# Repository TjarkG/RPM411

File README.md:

# RPM411
Reverse Engineering of the Vaisala RPM411 Pressur Sensor for the RS41 Radiosonde 

For information about the RS41 see [Bajzos website](https://sondehunt.de/language/en/vaisala-rs41), for schematics of it [the Radiosonde Hardware Repo](https://github.com/bazjo/radiosonde_hardware/tree/master/Vaisala_RS41).

The Schematic is in Kicad format, the Parts overlay in svg and can be edited with Inkscape. Some scans in jpeg are provided too.

Pull requests with improvements, translations and bug fixes are welcome!

# Introduction
The sonde is to be divided into three functional blocks, which are seperated by dotted lines in the Schematic.

* [Power Supply](#powersupply)
* [Microcontroller](#microcontroller)
* [Frontend](#frontend)
* [Connector](#connector)

Microcontroller (hidden by a shield with sticker) and Connector are on the Sonde facing side of the PCB, while the Front end usses almost the entire other side, with its power supply weged in the bottom left corner.

Reverse engineering is simpliefied by the fact that the blocks are essentialy smaller Versions of there RS41 counterparts, sharing many parts. A significant Part of this describtion is therfore the same as for the RS41 with different Part numbers.

# Schematic

## Powersupply
The powersupply (middle right) consists of a Low Dropout Regulator
[TVS70030](http://www.ti.com/lit/ds/symlink/tlv700-q1.pdf) from TI (`U7`), generating 3.3V for the frontend (the MCU is supplyed directly by the Sonde). Pin 4 of the LDO, which is NC according to the datasheet, is decoupled against ground, probably so that pin compatible versions like the [MAX8887](https://datasheets.maximintegrated.com/en/ds/MAX8887-MAX8888.pdf) can be used.

## Microcontroller
The microcontroller is a [STM32F100C8](https://www.st.com/resource/en/datasheet/stm32f100c8.pdf) `U1` from ST in LQFP48 package, the same model as in the Sonde itself, running from an internall clock. Like in the RS41, RC low pass filters are present at many outputs and resistors at many inputs

## Frontend

Electrically, the Frontend is very similar to the RS41's Humindity Messurment, but simplified because there is no temperature Messurment or Heating and all Components are on the PCB. In addition to the Pressure Sensor `P1`, a 15pF reference Capacitor `C33` is available.

The frontend consists of a ring oscillator, whose frequency is varied by variable impedances (e.g. the sensors) inserted into the feedback path with the help of analog switches.

Each ring oscillator is formed by a [74LVC3G04](https://assets.nexperia.com/documents/data-sheet/74LVC3G04.pdf) Triple Inverter `U5`. The three inverters are connected in series. The first and third inverter are feedbacked directly via an RC series element `C26`/`R31`, `R29`/`C23`, the entire ring oscillator via a capacitor `C19`. The ring oscillators can be pulled to +3V by a P-channel MOSFET `Q1` at the first inverter with separate control, which corresponds to ground at the output, to deactivate them.

The feedback path consists of a [74LVC1G32](https://assets.nexperia.com/documents/data-sheet/74LVC1G32.pdf) Or-Gate `U6` used as an Buffer and two resistors `R28` and `R30`, which probably are used for the fine tuning of the resonance frequency. This is followed by three single pole single throw (SPST) switches [TS5A9411](http://www.ti.com/lit/ds/symlink/ts5a9411.pdf) `U2-4`, the NO of which is connected to the output of the buffer and which switch the measuring and reference capacitor either into the feedback network or to ground. `U3` has no connection between COM and the input of the first buffer, where there should normally be a reference capacitor, so this switch does not serve any obvious purpose. However, since it is driven in software like the other two, it can be assumed that the switches have an example-independent non-linear effect on the feedback frequency measured at this switch to compensate for it. Parallel to the switches, fixed feedback is applied via the resistor `R32`.

The measurement output is sent to the MCU via `R8` and `R33`.

## Connector

`J1` connects the Board to the RS41's SPI bus, a clock and a Chip Select, one of which is shared with the EEPROM, as well as 3V MCU voltage shared with the STM32 on the Sonde and the EEPROM and 3.8V from the boost converter used to supply the Frontend via `U7`. From the six Pins that aren't connected on the RS41, five are used for an SWD interface, the MCU Reset pin and an UART and one remains unused.

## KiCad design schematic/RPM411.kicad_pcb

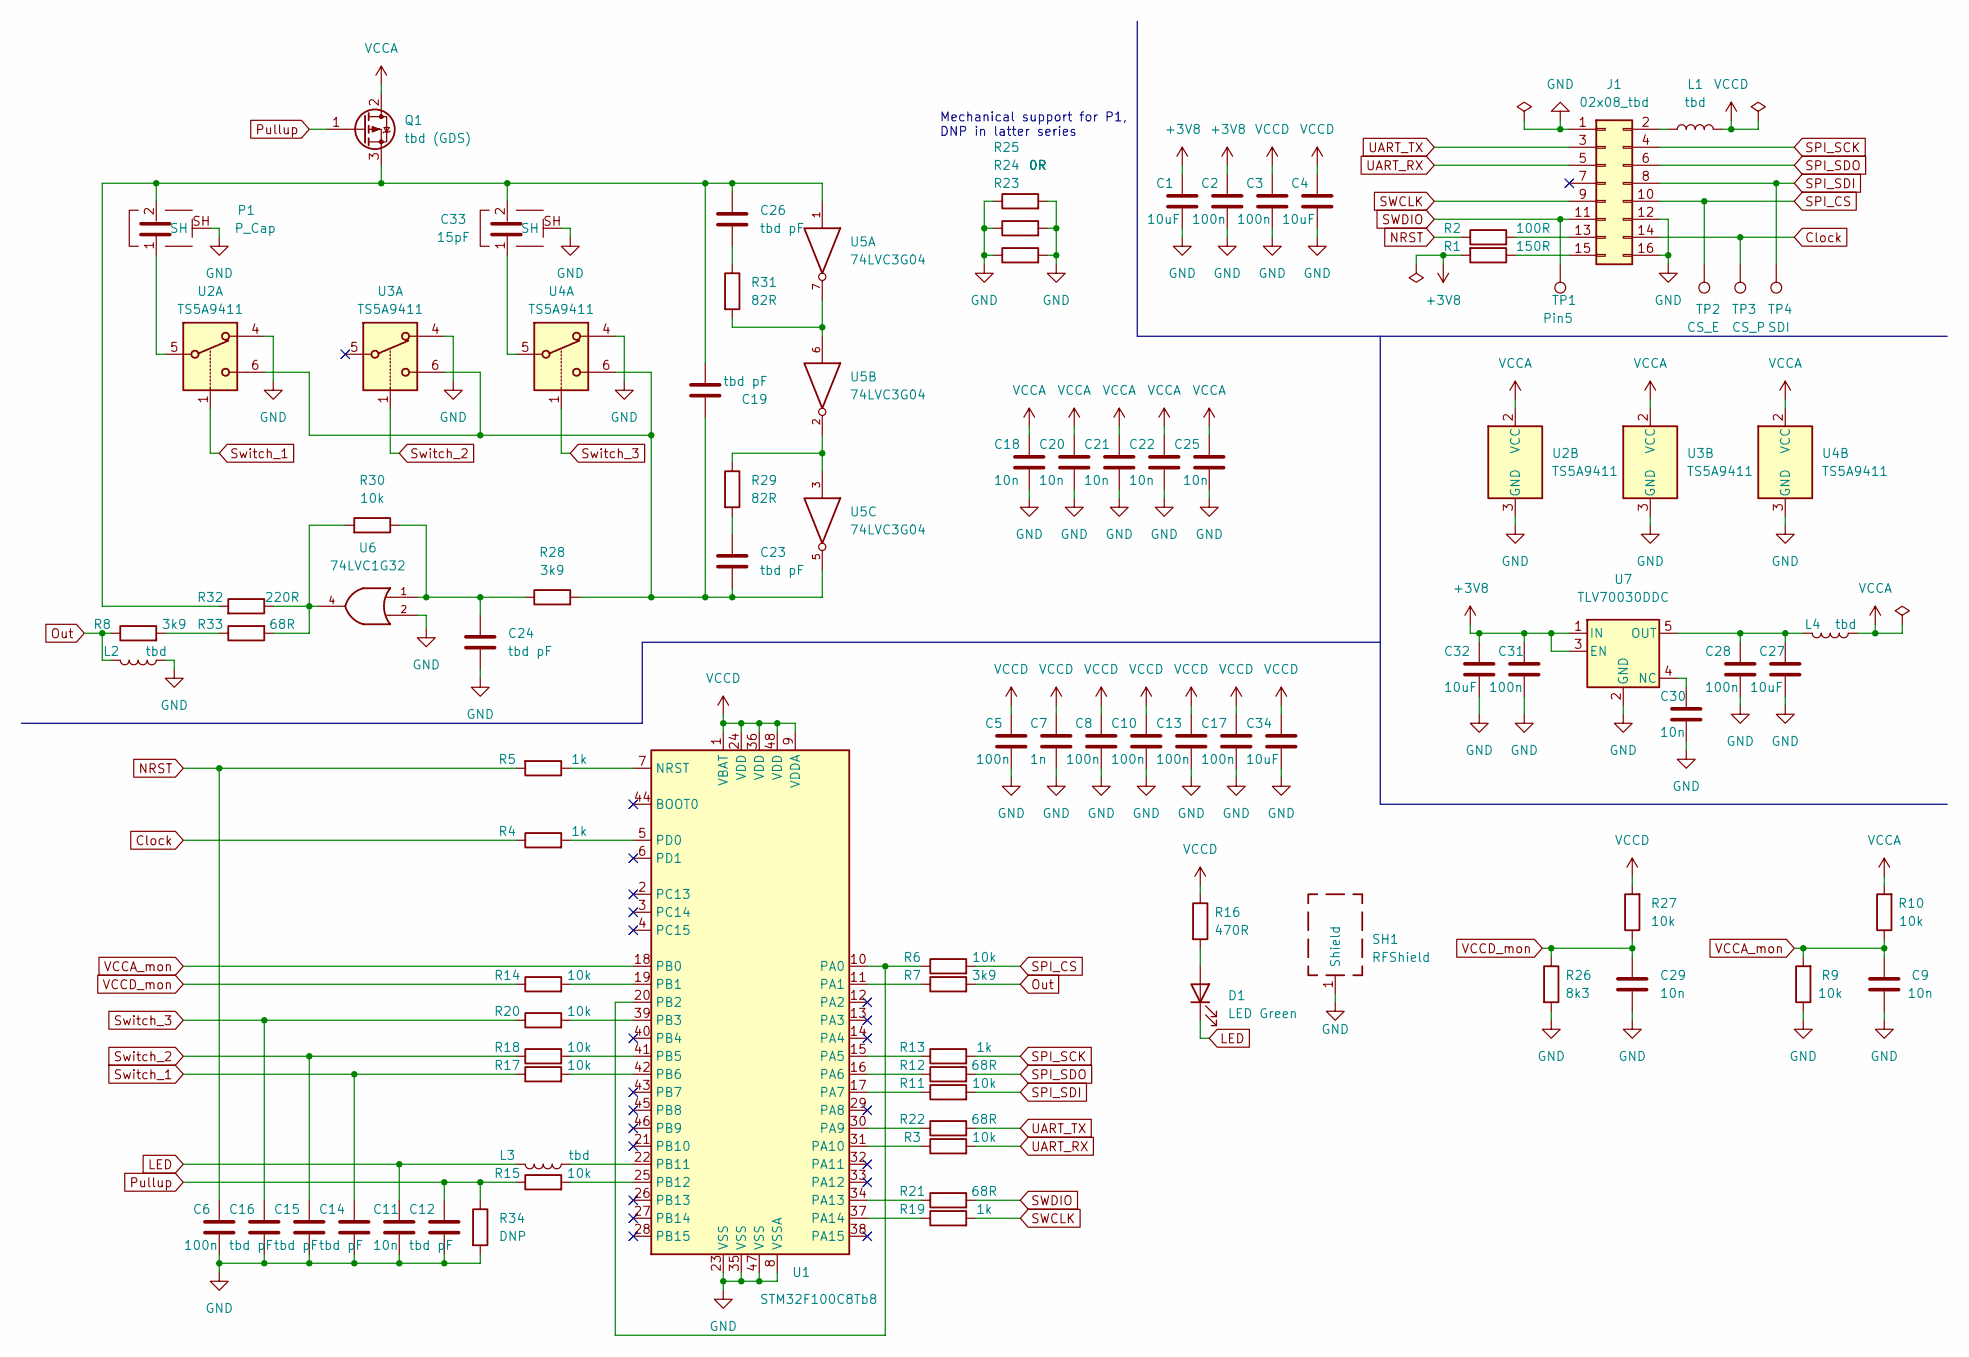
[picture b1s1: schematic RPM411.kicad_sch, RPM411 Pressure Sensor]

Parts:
C1, C4, C27, C32, C34: 10uF; C_0805_2012Metric
C2, C3, C5, C6, C8, C10, C13, C17, C28, C31: 100n; C_0402_1005Metric
C7: 1n; C_0402_1005Metric
C9, C11, C18, C20, C21, C22, C25, C29, C30: 10n; C_0402_1005Metric
C12, C14, C15, C16, C19, C23, C24, C26: tbd pF; C_0402_1005Metric
C33: 15pF; Cap_Shield
D1: LED Green; LED_0805_2012Metric
J1: 02x08_tbd; PinHeader_2x08_P1.00mm_Vertical
L1, L2, L3, L4: tbd; L_0402_1005Metric
P1: P_Cap; Pressure_Cap
Q1: tbd (GDS); SOT-523
R1: 150R; R_0402_1005Metric
R2: 100R; R_0402_1005Metric
R3, R6, R9, R10, R11, R14, R15, R17, R18, R20, R27, R30: 10k; R_0402_1005Metric
R4, R5, R13, R19: 1k; R_0402_1005Metric
R7, R8, R28: 3k9; R_0402_1005Metric
R12, R21, R22, R33: 68R; R_0402_1005Metric
R16: 470R; R_0402_1005Metric
R23, R24, R25: 0R; R_0402_1005Metric
R26: 8k3; R_0402_1005Metric
R29, R31: 82R; R_0402_1005Metric
R32: 220R; R_0402_1005Metric
R34: DNP; R_0402_1005Metric
SH1: RFShield; RMP411_Shield
TP1: Pin5; TestPoint_Pad_D1.0mm
TP2: CS_E; TestPoint_Pad_D1.0mm
TP3: CS_P; TestPoint_Pad_D1.0mm
TP4: SDI; TestPoint_Pad_D1.0mm
U1: STM32F100C8Tb8; LQFP-48_7x7mm_P0.5mm
U2, U3, U4: TS5A9411; SOT-363_SC-70-6
U5: 74LVC3G04; SSOP-8_3.95x5.21x3.27mm_P1.27mm
U6: 74LVC1G32; SOT-353_SC-70-5
U7: TLV70030DDC; SOT-23-5

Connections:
+3V8: C1.1, C2.1, C31.1, C32.1, R1.2, U7.1 (IN), U7.3 (EN)
CS_EEPROM: J1.10, R6.2, TP2.1
CS_Pressure: J1.14, R4.1, TP3.1
GND: C1.2, C2.2, C3.2, C4.2, C5.2, C6.2, C7.2, C8.2, C9.1, C10.2, C11.2, C12.1, C13.2, C14.2, C15.2, C16.2, C17.2, C18.2, C20.2, C21.2, C22.2, C24.2, C25.2, C27.2, C28.2, C29.2, C30.2, C31.2, C32.2, C33.SH, C34.2, J1.1, J1.12, J1.16, L2.1, P1.SH, R9.1, R23.1, R23.2, R24.1, R24.2, R25.1, R25.2, R26.2, R34.2, SH1.1 (Shield), U1.8 (VSSA), U1.23 (VSS), U1.35 (VSS), U1.47 (VSS), U2.3 (GND), U2.4, U3.3 (GND), U3.4, U4.3 (GND), U4.4, U5.4 (GND), U6.2, U6.3 (GND), U7.2 (GND)
LED: C11.1, D1.1 (K), L3.2
NRST: C6.1, R2.1, R5.2
unnamed: C23.1, R29.2
unnamed: C19.1, C26.1, C33.2, P1.2, Q1.3 (S), R32.2, U5.1
unnamed: D1.2 (A), R16.2
unnamed: J1.2, L1.1
unnamed: J1.13, R2.2
unnamed: J1.15, R1.1
unnamed: R4.2, U1.5 (PD0)
unnamed: R5.1, U1.7 (NRST)
unnamed: R7.1, U1.11 (PA1)
unnamed: R14.2, U1.19 (PB1)
unnamed: R20.2, U1.39 (PB3)
unnamed: R29.1, U5.2, U5.3
unnamed: C26.2, R31.1
unnamed: R31.2, U5.6, U5.7
unnamed: R30.2, R32.1, R33.2, U6.4
unnamed: R8.2, R33.1
unnamed: R13.1, U1.15 (PA5)
unnamed: R12.1, U1.16 (PA6)
unnamed: R11.1, U1.17 (PA7)
unnamed: R6.1, U1.10 (PA0), U1.20 (PB2)
unnamed: L3.1, U1.22 (PB11)
unnamed: R15.2, U1.25 (PB12)
unnamed: R22.1, U1.30 (PA9)
unnamed: R3.1, U1.31 (PA10)
unnamed: R21.1, U1.34 (PA13)
unnamed: R19.1, U1.37 (PA14)
unnamed: R18.2, U1.41 (PB5)
unnamed: R17.2, U1.42 (PB6)
unnamed: P1.1, U2.5
unnamed: C33.1, U4.5
unnamed: C19.2, C23.2, R28.2, U2.6, U3.6, U4.6, U5.5
unnamed: C24.1, R28.1, R30.1, U6.1
unnamed: C30.1, U7.4 (NC)
unnamed: C27.1, C28.1, L4.2, U7.5 (OUT)
Out: L2.2, R7.2, R8.1
Pullup: C12.2, Q1.1 (G), R15.1, R34.1
SPI_SCK: J1.4, R13.2
SPI_SDI: J1.8, R11.2, TP4.1
SPI_SDO: J1.6, R12.2
SWCLK: J1.9, R19.2
SWDIO: J1.11, R21.2, TP1.1
Switch_1: C14.1, R17.1, U2.1
Switch_2: C15.1, R18.1, U3.1
Switch_3: C16.1, R20.1, U4.1
UART_RX: J1.5, R3.2
UART_TX: J1.3, R22.2
VCC: C18.1, C20.1, C21.1, C22.1, C25.1, L4.1, Q1.2 (D), R10.2, U2.2 (VCC), U3.2 (VCC), U4.2 (VCC), U5.8 (VCC), U6.5 (VCC)
VCCA_mon: C9.2, R9.2, R10.1, U1.18 (PB0)
VCCD_mon: C29.1, R14.1, R26.1, R27.1
VDD: C3.1, C4.1, C5.1, C7.1, C8.1, C10.1, C13.1, C17.1, C34.1, L1.2, R16.1, R27.2, U1.1 (VBAT), U1.9 (VDDA), U1.24 (VDD), U1.36 (VDD), U1.48 (VDD)

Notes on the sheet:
Mechanical support for P1, DNP in latter series

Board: 2 copper layers, 88 parts (0 on the bottom side), 56 nets, no tracks yet.

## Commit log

2022-07-20 added scans/photos
2022-07-20 started drawing overlay
2022-07-20 traced traces
2022-07-21 added temporaray numbering to overlay
2022-07-21 initialzed schematic with all passivs
2022-07-21 Updated Overlay with proper names
2022-07-21 added pressure cap
2022-07-22 added stacked scans
2022-07-22 identified ICs
2022-07-22 added ground connections
2022-07-23 completed schematic
2022-07-23 fixed erc errors
2022-07-23 sorted schematic
2022-07-23 cleaned up folders
2022-07-23 removed Partlist (Can be replacd by BOM)
2022-07-24 updated schematic picture
2022-07-25 started describtion
2022-07-26 completed circuit discribtion
2022-07-26 formating
2022-07-26 renamed CS Signals
2022-07-29 fixed number of CS Signals in describtion
